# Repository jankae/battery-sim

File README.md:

# battery-sim

## What is it?
The device emulates the behaviour of a battery, essentially it is a two quadrant supply with a configurable internal resistance.

Key features:
* Voltage range: 0 to 18V
* Current range: -3 to +3A
* Resistance range: 0.005 to 6Ohm

## Why was it built?
While developing other hardware meant to test batteries, various batteries in various different states (voltages, internal resistances, ...) were required to test some aspects. Normal batteries could have been used but getting them to (repeatedly!) behave in the necessary way would have been extremely time-consuming. So, this device was created.

It also doubles as a battery charger/discharger and general use supply.

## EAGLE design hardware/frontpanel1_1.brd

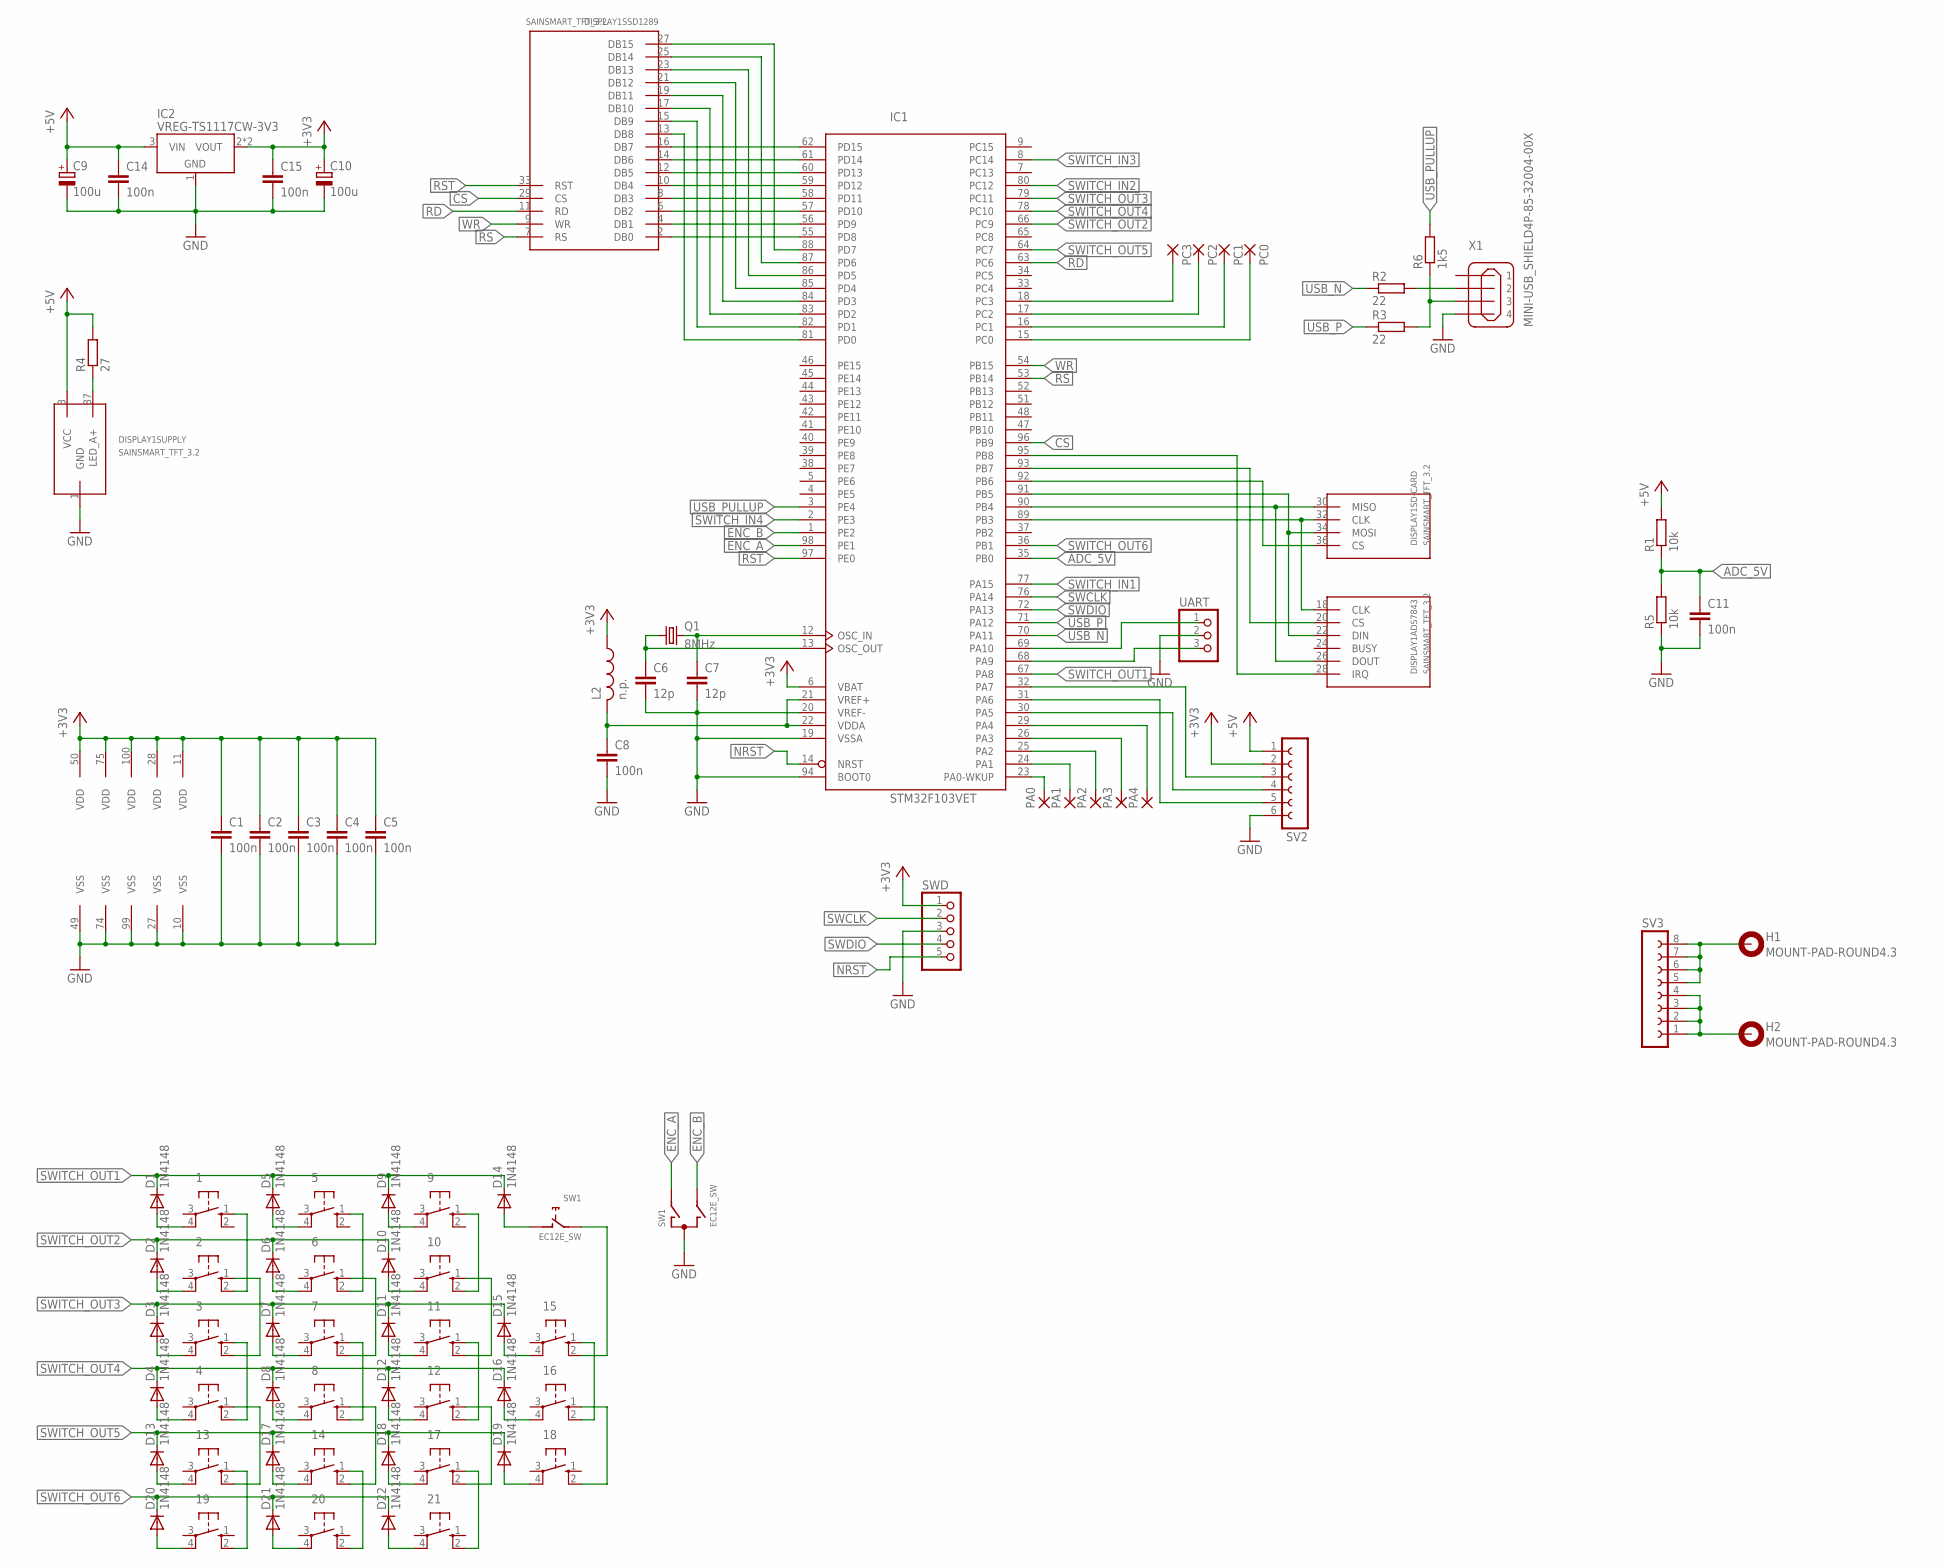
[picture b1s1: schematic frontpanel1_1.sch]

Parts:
1, 2, 3, 4, 5, 6, 7, 8, 9, 10, 11, 12, 13, 14, 15, 16, 17, 18, 19, 20, 21: 10-XXSMD; SMD
C1, C2, C3, C4, C5, C8, C11, C14, C15: 100n; C0603K
C6, C7: 12p; C0603K
C9, C10: 100u; 153CLV-0505
D1, D2, D3, D4, D5, D6, D7, D8, D9, D10, D11, D12, D13, D14, D15, D16, D17, D18, D19, D20, D21, D22: 1N4148; SOD323-W
DISPLAY1: SAINSMART_TFT_3.2
H1, H2: MOUNT-PAD-ROUND4.3; 4,3-PAD
IC1: STM32F103VET; LQFP100
IC2: VREG-TS1117CW-3V3; SOT223
L2: n.p.; R0603
PA0, PA1, PA2, PA3, PA4: SMD2; SMD1,27-2,54
PC0, PC1, PC2, PC3: SMD2; SMD1,27-2,54
Q1: 8MHz; SM49
R1, R5: 10k; R0603
R2, R3: 22; R0603
R4: 27; R1206
R6: 1k5; R0603
SV2: FE06-1; FE06
SV3: FE08-1; FE08
SW1: EC12E_SW; ALPS_EC12E_SW
SWD: PINHD-1X5; 1X05
UART: PINHD-1X3; 1X03
X1: MINI-USB_SHIELD4P-85-32004-00X; 85-32004-00X

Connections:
+3V3: C1.1, C2.1, C3.1, C4.1, C5.1, C10.+, C15.1, IC1.6 (VBAT), IC1.11 (VDD), IC1.28 (VDD), IC1.50 (VDD), IC1.75 (VDD), IC1.100 (VDD), IC2.2 (VOUT), IC2.4 (VOUT), L2.1, SV2.2, SWD.1
+5V: C9.+, C14.1, DISPLAY1.3 (VCC), IC2.3 (VIN), R1.2, R4.2, SV2.1
ADC_5V: C11.1, IC1.35 (PB0), R1.1, R5.2
CS: DISPLAY1.29 (CS), IC1.96 (PB9)
ENC_A: IC1.98 (PE1), SW1.A
ENC_B: IC1.1 (PE2), SW1.B
EXT4: C8.1, IC1.21 (VREF+), IC1.22 (VDDA), L2.2
GND: C1.2, C2.2, C3.2, C4.2, C5.2, C6.2, C7.2, C8.2, C9.-, C10.-, C11.2, C14.2, C15.2, DISPLAY1.1 (GND), IC1.10 (VSS), IC1.19 (VSSA), IC1.20 (VREF-), IC1.27 (VSS), IC1.49 (VSS), IC1.74 (VSS), IC1.94 (BOOT0), IC1.99 (VSS), IC2.1 (GND), R5.1, SV2.6, SW1.C, SWD.3, UART.2, X1.4
MISO: IC1.31 (PA6), SV2.5
MOSI: IC1.32 (PA7), SV2.3
unnamed: IC1.15 (PC0), PC0.1
unnamed: C7.1, IC1.12 (OSC_IN), Q1.2
unnamed: C6.1, IC1.13 (OSC_OUT), Q1.1
unnamed: DISPLAY1.2 (DB0), IC1.55 (PD8)
unnamed: DISPLAY1.4 (DB1), IC1.56 (PD9)
unnamed: DISPLAY1.6 (DB2), IC1.57 (PD10)
unnamed: DISPLAY1.8 (DB3), IC1.58 (PD11)
unnamed: DISPLAY1.10 (DB4), IC1.59 (PD12)
unnamed: DISPLAY1.12 (DB5), IC1.60 (PD13)
unnamed: DISPLAY1.14 (DB6), IC1.61 (PD14)
unnamed: DISPLAY1.16 (DB7), IC1.62 (PD15)
unnamed: DISPLAY1.15 (DB9), IC1.82 (PD1)
unnamed: DISPLAY1.17 (DB10), IC1.83 (PD2)
unnamed: DISPLAY1.13 (DB8), IC1.81 (PD0)
unnamed: DISPLAY1.19 (DB11), IC1.84 (PD3)
unnamed: DISPLAY1.21 (DB12), IC1.85 (PD4)
unnamed: DISPLAY1.23 (DB13), IC1.86 (PD5)
unnamed: DISPLAY1.25 (DB14), IC1.87 (PD6)
unnamed: DISPLAY1.27 (DB15), IC1.88 (PD7)
unnamed: 13.1 (S), 19.2 (S1)
unnamed: 4.1 (S), 13.2 (S1)
unnamed: 13.4 (P1), D13.A
unnamed: 14.4 (P1), D17.A
unnamed: 17.4 (P1), D18.A
unnamed: 18.4 (P1), D19.A
unnamed: 19.4 (P1), D20.A
unnamed: 20.4 (P1), D21.A
unnamed: 21.4 (P1), D22.A
unnamed: IC1.16 (PC1), PC1.1
unnamed: IC1.17 (PC2), PC2.1
unnamed: IC1.18 (PC3), PC3.1
unnamed: IC1.23 (PA0-WKUP), PA0.1
unnamed: 2.1 (S), 3.2 (S1)
unnamed: 1.1 (S), 2.2 (S1)
unnamed: 5.1 (S), 6.2 (S1)
unnamed: 6.1 (S), 7.2 (S1)
unnamed: IC1.24 (PA1), PA1.1
unnamed: 8.1 (S), 14.2 (S1)
unnamed: 14.1 (S), 20.2 (S1)
unnamed: 17.1 (S), 21.2 (S1)
unnamed: IC1.25 (PA2), PA2.1
unnamed: R2.2, X1.2
unnamed: R3.2, R6.1, X1.3
unnamed: DISPLAY1.37 (LED_A+), R4.1
unnamed: IC1.26 (PA3), PA3.1
unnamed: DISPLAY1.22 (DIN), DISPLAY1.34 (MOSI), IC1.91 (PB5)
unnamed: 4.4 (P1), D4.A
unnamed: 3.4 (P1), D3.A
unnamed: 2.4 (P1), D2.A
unnamed: 1.4 (P1), D1.A
unnamed: DISPLAY1.26 (DOUT), DISPLAY1.30 (MISO), IC1.90 (PB4)
unnamed: DISPLAY1.18 (CLK), DISPLAY1.32 (CLK), IC1.89 (PB3)
unnamed: 11.1 (S), 12.2 (S1)
unnamed: 8.4 (P1), D8.A
unnamed: 7.4 (P1), D7.A
unnamed: 6.4 (P1), D6.A
unnamed: 5.4 (P1), D5.A
unnamed: 10.1 (S), 11.2 (S1)
unnamed: 9.1 (S), 10.2 (S1)
unnamed: 15.1 (S), 16.2 (S1)
unnamed: 12.4 (P1), D12.A
unnamed: 11.4 (P1), D11.A
unnamed: 10.4 (P1), D10.A
unnamed: 9.4 (P1), D9.A
unnamed: IC1.29 (PA4), PA4.1
unnamed: DISPLAY1.36 (CS), IC1.92 (PB6)
unnamed: DISPLAY1.20 (CS), IC1.93 (PB7)
unnamed: 16.4 (P1), D16.A
unnamed: 15.4 (P1), D15.A
unnamed: D14.A, SW1.D (1)
unnamed: DISPLAY1.28 (IRQ), IC1.95 (PB8)
unnamed: 15.2 (S1), SW1.E (2)
NRST: IC1.14 (NRST), SWD.5
OUT+: H2.B4,3, SV3.1, SV3.2, SV3.3, SV3.4
OUT-: H1.B4,3, SV3.5, SV3.6, SV3.7, SV3.8
RD: DISPLAY1.11 (RD), IC1.63 (PC6)
RS: DISPLAY1.7 (RS), IC1.53 (PB14)
RST: DISPLAY1.33 (RST), IC1.97 (PE0)
RX: IC1.69 (PA10), UART.1
SCK: IC1.30 (PA5), SV2.4
SWCLK: IC1.76 (PA14), SWD.2
SWDIO: IC1.72 (PA13), SWD.4
SWITCH_IN1: 3.1 (S), 4.2 (S1), IC1.77 (PA15)
SWITCH_IN2: 7.1 (S), 8.2 (S1), IC1.80 (PC12)
SWITCH_IN3: 12.1 (S), 17.2 (S1), IC1.8 (PC14)
SWITCH_IN4: 16.1 (S), 18.2 (S1), IC1.2 (PE3)
SWITCH_OUT1: D1.C, D5.C, D9.C, D14.C, IC1.67 (PA8)
SWITCH_OUT2: D2.C, D6.C, D10.C, IC1.66 (PC9)
SWITCH_OUT3: D3.C, D7.C, D11.C, D15.C, IC1.79 (PC11)
SWITCH_OUT4: D4.C, D8.C, D12.C, D16.C, IC1.78 (PC10)
SWITCH_OUT5: D13.C, D17.C, D18.C, D19.C, IC1.64 (PC7)
SWITCH_OUT6: D20.C, D21.C, D22.C, IC1.36 (PB1)
TX: IC1.68 (PA9), UART.3
USB_N: IC1.70 (PA11), R2.1
USB_P: IC1.71 (PA12), R3.1
USB_PULLUP: IC1.3 (PE4), R6.2
WR: DISPLAY1.9 (WR), IC1.54 (PB15)

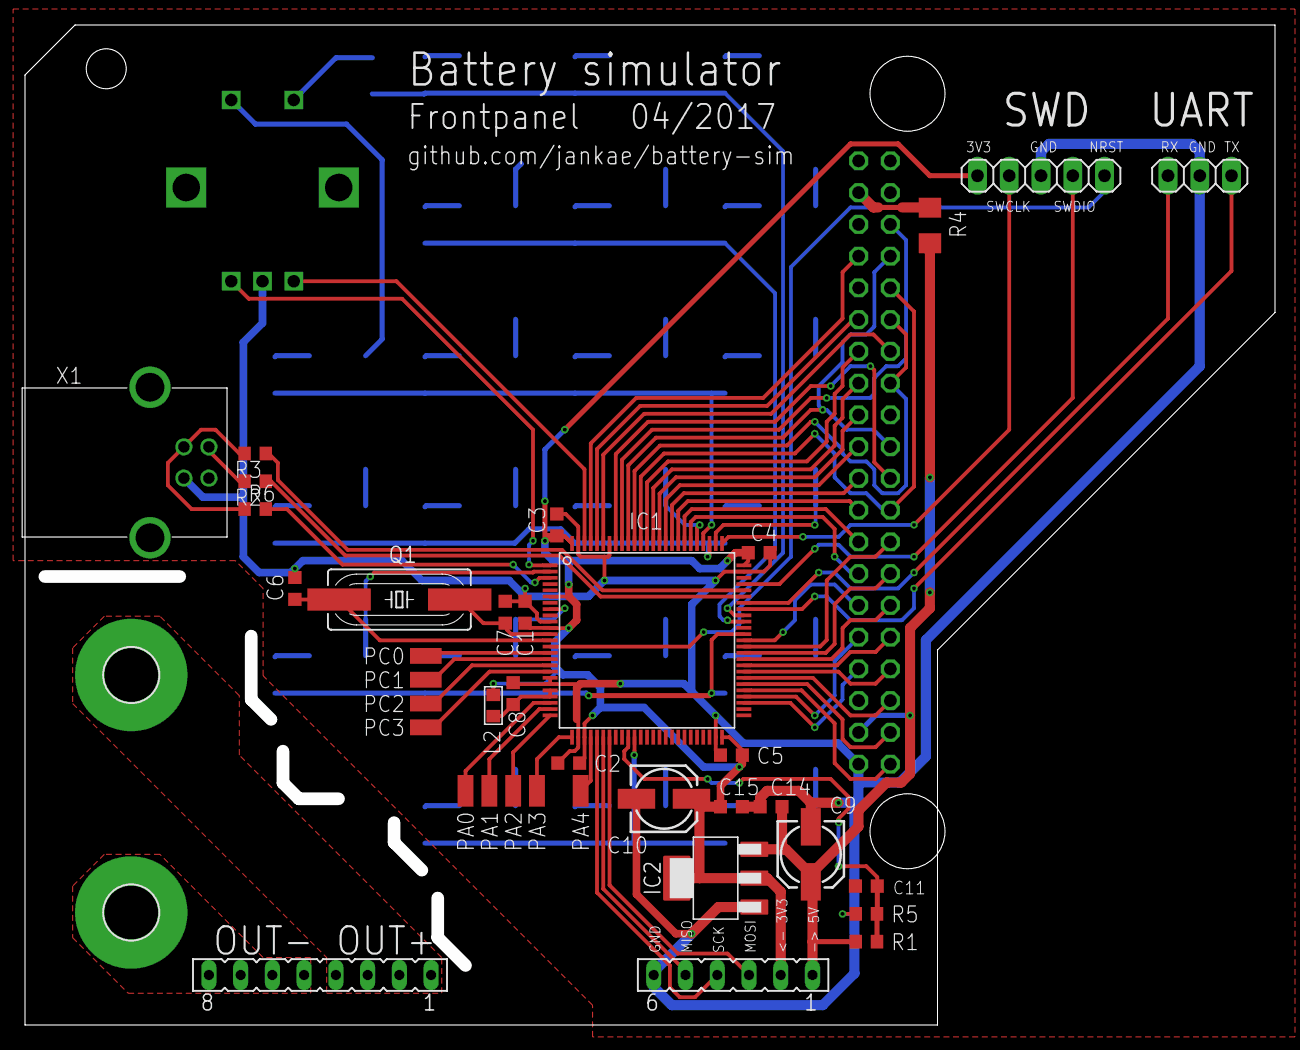
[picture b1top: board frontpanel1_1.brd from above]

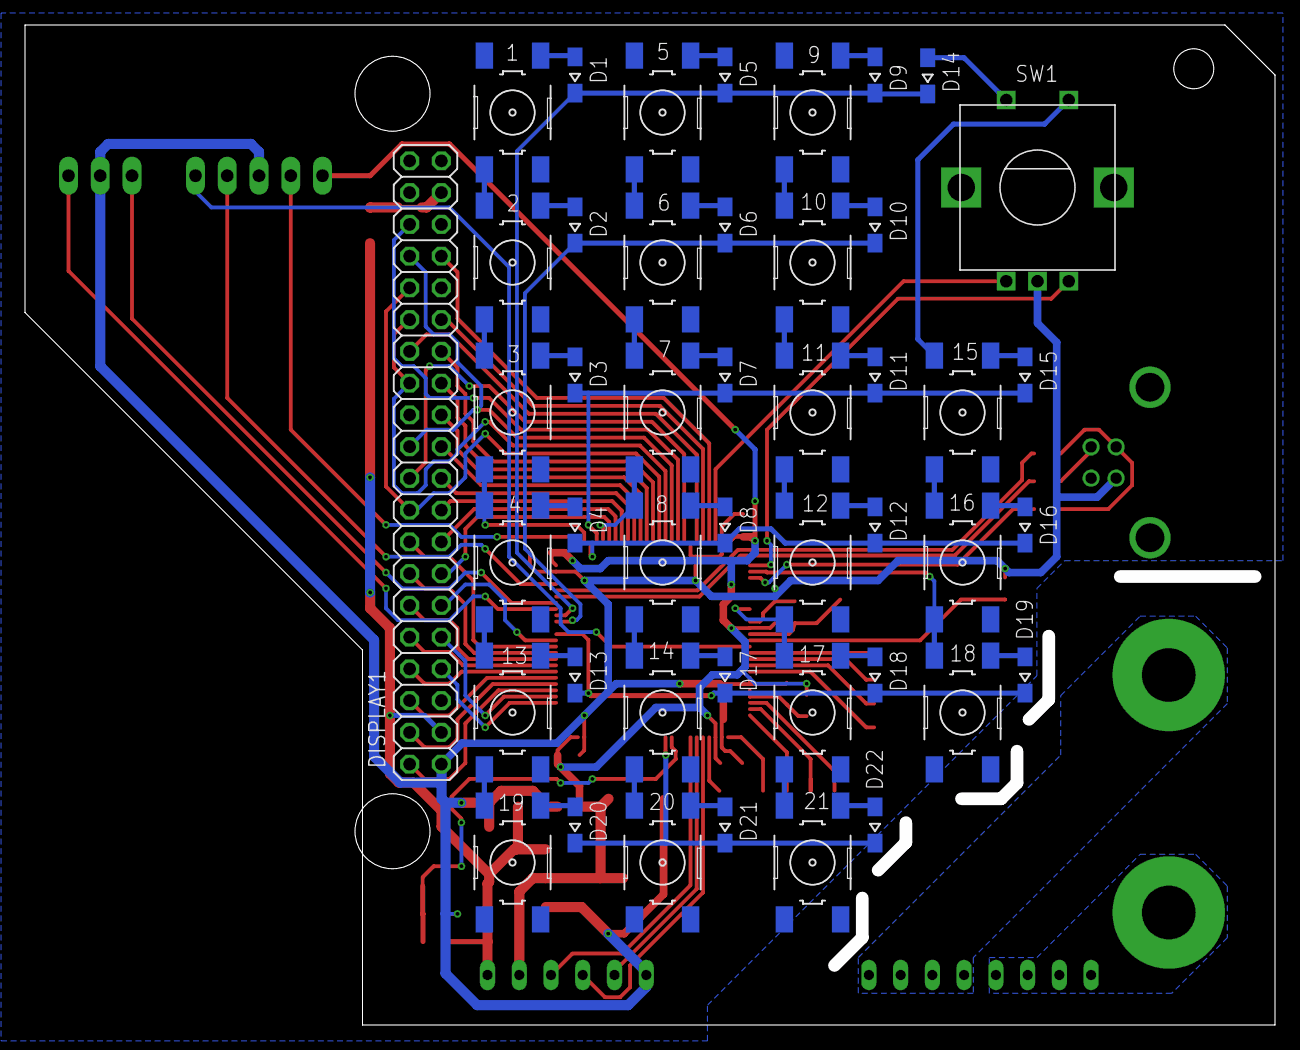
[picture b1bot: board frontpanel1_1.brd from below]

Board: 2 copper layers, 100.0 x 80.0 mm, 84 parts (45 on the bottom side), 107 nets.

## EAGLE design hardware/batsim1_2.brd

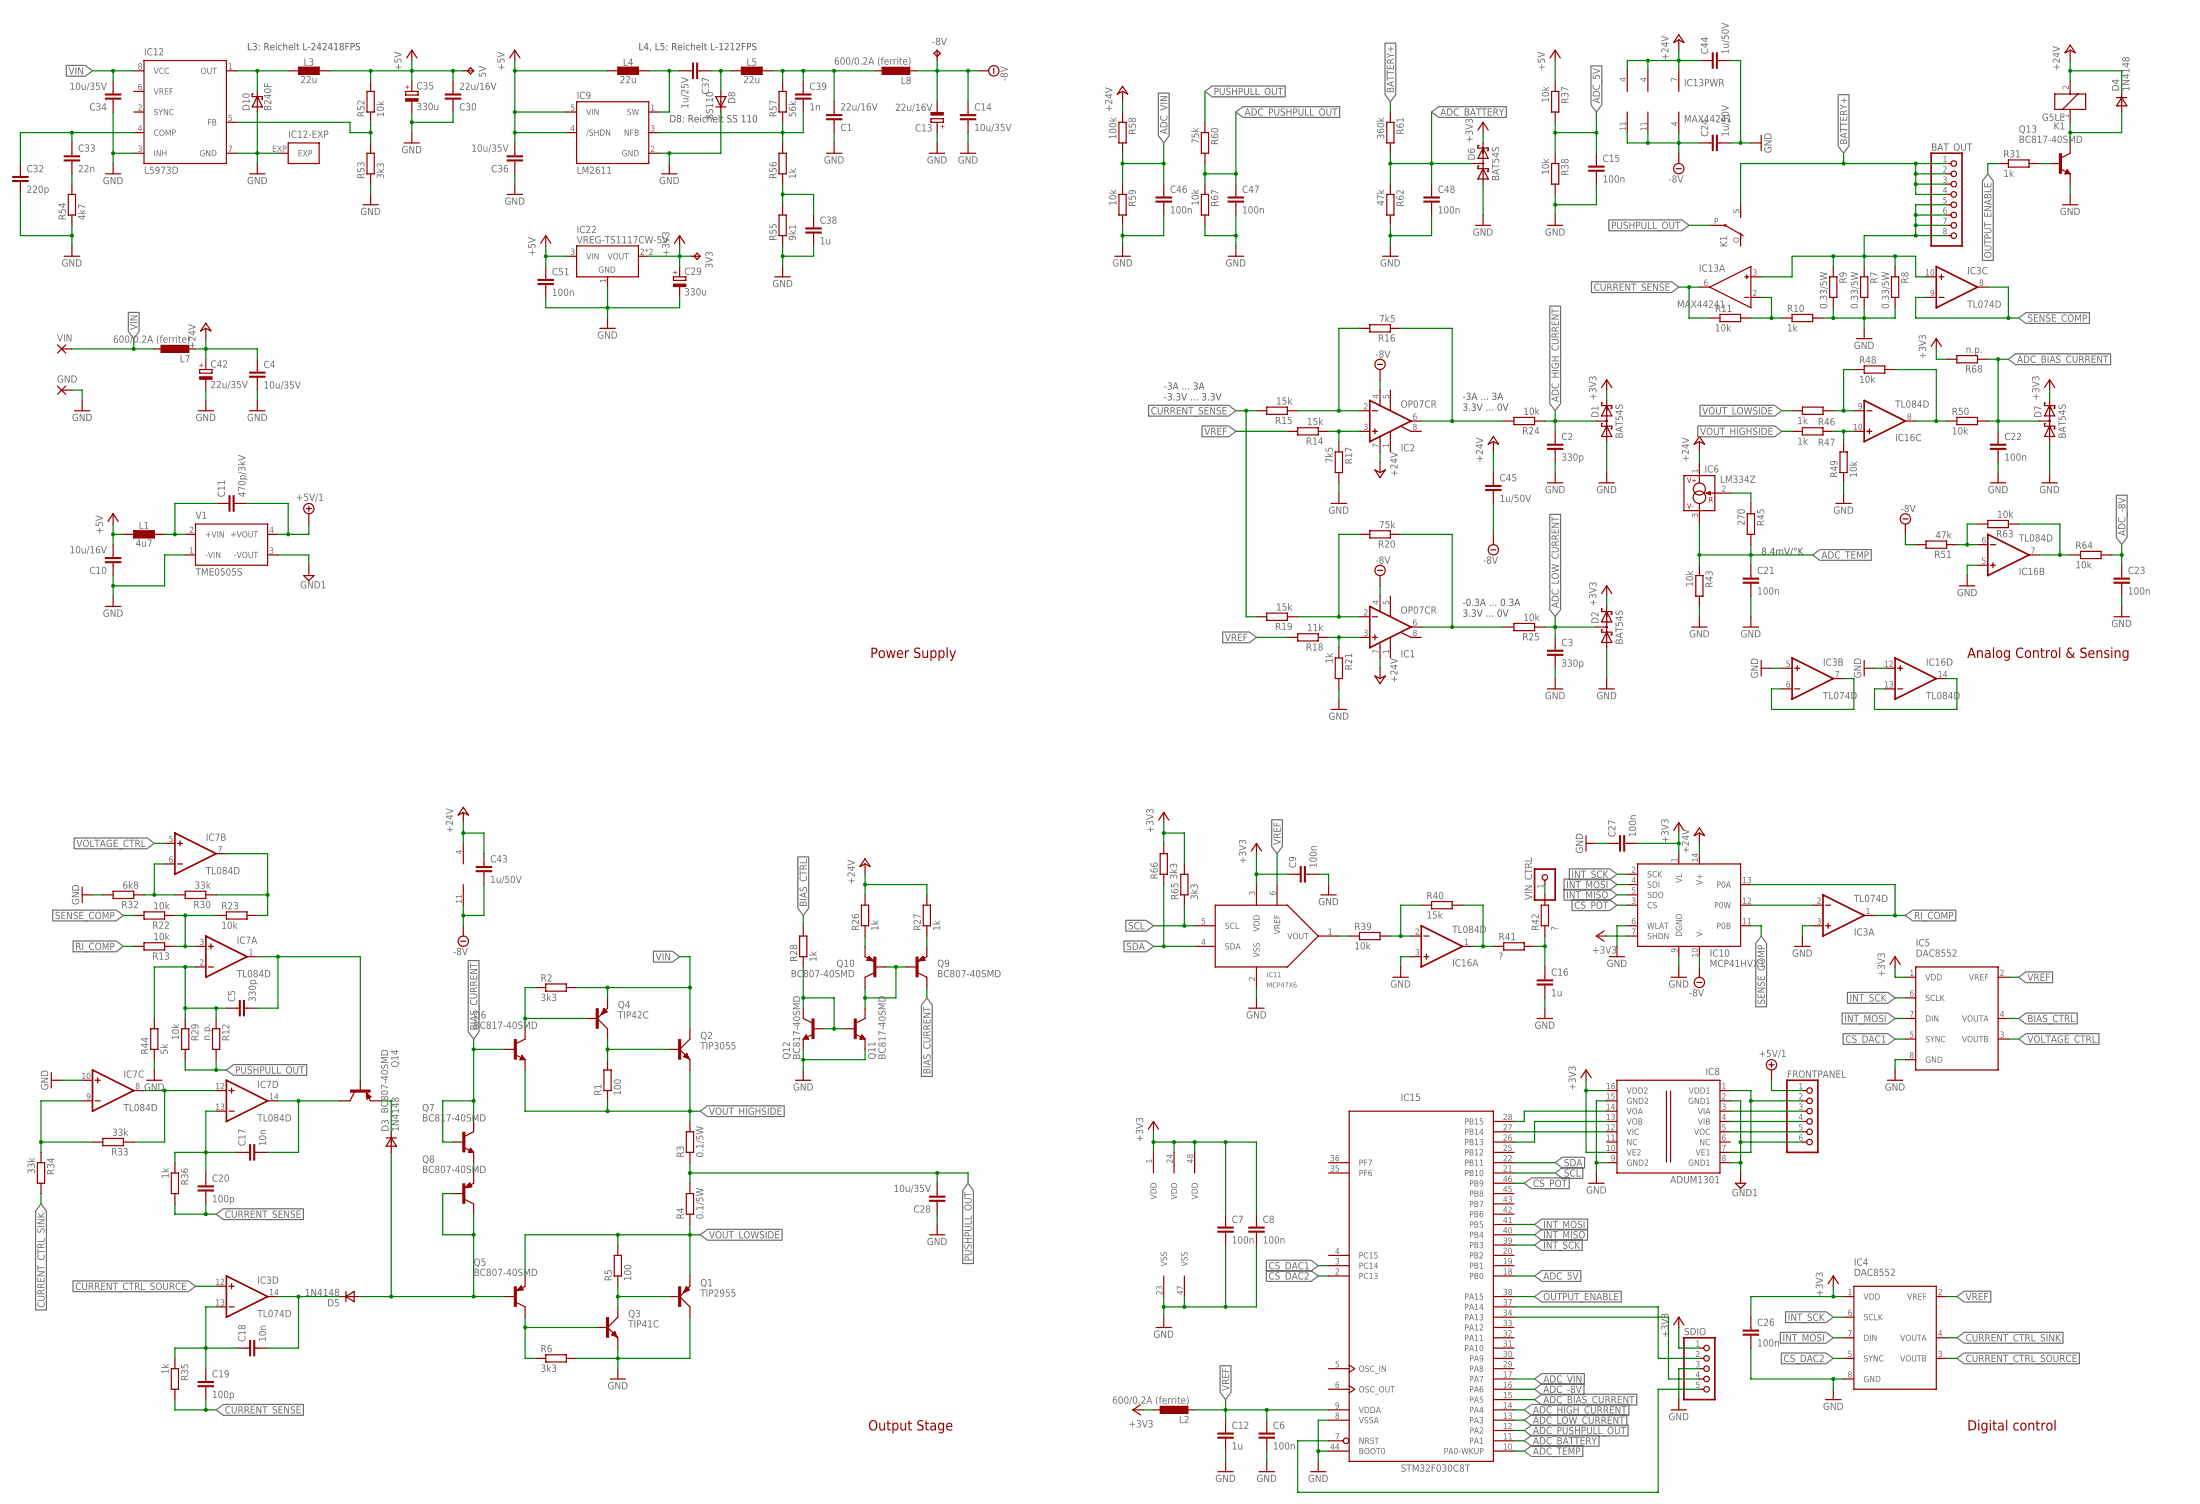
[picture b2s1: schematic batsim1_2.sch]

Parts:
3V3, 5V: TPB1,27; B1,27
-8V: TPB1,27; B1,27
BAT_OUT: PINHD-1X8/90; 1X08/90
C1, C30: 22u/16V; C1206
C2, C3, C5: 330p; C0603
C4, C14, C28, C34, C36: 10u/35V; C1206
C6, C7, C8, C9, C15, C21, C22, C23, C26, C27, C46, C47, C48, C51: 100n; C0603
C10: 10u/16V; C1206
C11: 470p/3kV; C1812
C12, C16, C38: 1u; C0603
C13: 22u/16V; 153CLV-0505
C17, C18: 10n; C0603
C19, C20: 100p; C0603
C24, C43, C44, C45: 1u/50V; C0603
C29, C35: 330u; 153CLV-0605
C32: 220p; C0603
C33: 22n; C0603
C37: 1u/25V; C1206
C39: 1n; C0603
C42: 22u/35V; 153CLV-0605
D1, D2, D6, D7: BAT54S; SOT23
D3, D4, D5: 1N4148; SOD323
D8: SS110; SMA
D10: B240F; SMB
FRONTPANEL: PINHD-1X6/90; 1X06/90
GND: 3,81/1,4
IC1, IC2: OP07CR; SO08
IC3: TL074D; SO14
IC4, IC5: DAC8552; MSOP8
IC6: LM334Z; TO92
IC7, IC16: TL084D; SO14
IC8: ADUM1301; SO-16W
IC9: LM2611; SOT23-5
IC10: MCP41HVX1; TSSOP14
IC11: MCP47X6; SOT23-6L
IC12: L5973D; HSOP8
IC13: MAX44241; UMAX8
IC15: STM32F030C8T; LQFP48
IC22: VREG-TS1117CW-5V; SOT223
K1: G5LE
L1: 4u7; L_1212
L2, L7, L8: 600/0.2A (ferrite); L2012C
L3: 22u; L_NR60XX
L4, L5: 22u; L_1212
Q1: TIP2955; TOP3AV
Q2: TIP3055; TOP3AV
Q3: TIP41C; TO220AV
Q4: TIP42C; TO220AV
Q5, Q8, Q9, Q10, Q14: BC807-40SMD; SOT23-BEC
Q6, Q7, Q11, Q12, Q13: BC817-40SMD; SOT23-BEC
R1, R5: 100; R0603
R2, R6, R53, R65, R66: 3k3; R0603
R3, R4: 0.1/5W; 5WAXIAL
R7, R8, R9: 0.33/5W; 5WAXIAL
R10, R21, R26, R27, R28, R31, R35, R36, R46, R47, R56: 1k; R0603
R11, R13, R22, R23, R24, R25, R29, R37, R38, R39, R43, R48, R49, R50, R52, R59, R63, R64, R67: 10k; R0603
R12, R68: n.p.; R0603
R14, R15, R19, R40: 15k; R0603
R16, R17: 7k5; R0603
R18: 11k; R0603
R20, R60: 75k; R0603
R30, R33, R34: 33k; R0603
R32: 6k8; R0603
R41, R42: ?; R0603
R44: 5k; R0603
R45: 270; R0603
R51, R62: 47k; R0603
R54: 4k7; R0603
R55: 9k1; R0603
R57: 56k; R0603
R58: 100k; R0603
R61: 360k; R0603
SDIO: PINHD-1X5; 1X05
V1: TME0505S; TME
VIN: 3,81/1,4
VIN_CTRL: PINHD-1X1; 1X01

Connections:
+3V3: 3V3.TP, C7.1, C8.1, C9.1, C26.1, C27.2, C29.+, D1.2 (C2), D2.2 (C2), D6.2 (C2), D7.2 (C2), IC4.1 (VDD), IC5.1 (VDD), IC8.10 (VE2), IC8.16 (VDD2), IC10.1 (VL), IC10.7 (SHDN), IC11.3 (VDD), IC15.1 (VDD), IC15.24 (VDD), IC15.48 (VDD), IC22.2 (VOUT), IC22.4 (VOUT), L2.1, R65.2, R66.2, R68.2, SDIO.1
+5V: 5V.TP, C10.2, C30.2, C35.+, C36.2, C51.1, IC9.4 (/SHDN), IC9.5 (VIN), IC22.3 (VIN), L1.1, L3.2, L4.1, R37.1, R52.2
+5V/1: C11.2, FRONTPANEL.1, V1.4 (+VOUT)
+24V: C4.1, C42.+, C43.1, C44.1, C45.1, D4.1 (C), IC1.7 (V+), IC2.7 (V+), IC3.4 (V+), IC6.1 (V+), IC7.4 (V+), IC10.14 (V+), IC13.7 (V+), IC16.4 (V+), K1.2, L7.2, R26.2, R27.2, R58.1
-8V: -8V.TP, C13.-, C14.1, C24.1, C43.2, C45.2, IC1.4 (V-), IC2.4 (V-), IC3.11 (V-), IC7.11 (V-), IC10.10 (V-), IC13.4 (V-), IC16.11 (V-), L8.2, R51.2
ADC_5V: C15.1, IC15.18 (PB0), R37.2, R38.1
ADC_-8V: C23.1, IC15.16 (PA6), R64.2
ADC_BATTERY: C48.1, D6.3 (C1A2), IC15.11 (PA1), R61.2, R62.1
ADC_BIAS_CURRENT: C22.1, D7.3 (C1A2), IC15.15 (PA5), R50.2, R68.1
ADC_HIGH_CURRENT: C2.1, D1.3 (C1A2), IC15.14 (PA4), R24.1
ADC_LOW_CURRENT: C3.1, D2.3 (C1A2), IC15.13 (PA3), R25.1
ADC_PUSHPULL_OUT: C47.1, IC15.12 (PA2), R60.2, R67.1
ADC_TEMP: C21.1, IC6.3 (V-), IC15.10 (PA0-WKUP), R43.1, R45.2
ADC_VIN: C46.1, IC15.17 (PA7), R58.2, R59.1
BATTERY+: BAT_OUT.1, BAT_OUT.2, BAT_OUT.3, BAT_OUT.4, K1.S, R61.1
BIAS_CTRL: IC5.4 (VOUTA), R28.2
BIAS_CURRENT: Q6.B, Q7.B, Q7.C, Q9.C
CS_DAC1: IC5.5 (SYNC), IC15.3 (PC14)
CS_DAC2: IC4.5 (SYNC), IC15.2 (PC13)
CS_POT: IC10.3 (CS), IC15.46 (PB9)
CURRENT_CTRL_SINK: IC4.4 (VOUTA), R34.2
CURRENT_CTRL_SOURCE: IC3.12 (+IN), IC4.3 (VOUTB)
CURRENT_SENSE: C19.2, C20.2, IC13.6 (OUT), R11.1, R15.2, R19.2, R35.2, R36.2
EXT_MISO: IC8.12 (VIC), IC15.27 (PB14)
EXT_MOSI: IC8.14 (VOA), IC15.28 (PB15)
EXT_SCK: IC8.13 (VOB), IC15.26 (PB13)
GND: C1.1, C2.2, C3.2, C4.2, C6.2, C7.2, C8.2, C9.2, C10.1, C12.2, C13.+, C14.2, C15.2, C16.2, C21.2, C22.2, C23.2, C24.2, C26.2, C27.1, C28.1, C29.-, C30.1, C32.2, C34.1, C35.-, C36.1, C38.2, C42.-, C44.2, C46.2, C47.2, C48.2, C51.2, D1.1 (A1), D2.1 (A1), D6.1 (A1), D7.1 (A1), D8.C, D10.A, GND.1, IC3.3 (+IN), IC3.5 (+IN), IC4.8 (GND), IC5.8 (GND), IC7.10 (+IN), IC8.9 (GND2), IC8.15 (GND2), IC9.2 (GND), IC10.6 (WLAT), IC10.9 (DGND), IC11.2 (VSS), IC12.3 (INH), IC12.7 (GND), IC12.EXP, IC15.8 (VSSA), IC15.23 (VSS), IC15.44 (BOOT0), IC15.47 (VSS), IC16.3 (+IN), IC16.5 (+IN), IC16.12 (+IN), IC22.1 (GND), Q1.C, Q3.E, Q11.E, Q12.E, Q13.E, R6.2, R7.2, R8.2, R9.2, R10.2, R17.2, R21.2, R32.2, R38.2, R43.2, R44.1, R49.1, R53.1, R54.1, R55.1, R59.2, R62.2, R67.2, SDIO.3, V1.1 (-VIN)
GND1: FRONTPANEL.6, IC8.2 (GND1), IC8.8 (GND1), V1.3 (-VOUT)
INT_MISO: IC10.5 (SDO), IC15.40 (PB4)
INT_MOSI: IC4.7 (DIN), IC5.7 (DIN), IC10.4 (SDI), IC15.41 (PB5)
INT_SCK: IC4.6 (SCLK), IC5.6 (SCLK), IC10.2 (SCK), IC15.39 (PB3)
LM2611_SW: C37.2, IC9.1 (SW), L4.2
unnamed: IC7.3 (+IN), R13.1, R22.1, R23.1
unnamed: Q2.B, Q4.C, R1.2
unnamed: Q4.B, Q6.C, R2.1
unnamed: IC7.6 (-IN), R30.2, R32.1
unnamed: BAT_OUT.5, BAT_OUT.6, BAT_OUT.7, BAT_OUT.8, IC3.10 (+IN), IC13.3 (IN+), R7.1, R8.1, R9.1
unnamed: IC16.9 (-IN), R46.2, R48.1
unnamed: Q1.B, Q3.C, R5.1
unnamed: C11.1, L1.2, V1.2 (+VIN)
unnamed: Q3.B, Q5.C, R6.1
unnamed: Q7.E, Q8.E
unnamed: IC7.7 (OUT), R23.2, R30.1
unnamed: D3.1 (C), Q14.E
unnamed: D4.2 (A), K1.1, Q13.C
unnamed: IC13.2 (IN-), R10.1, R11.2
unnamed: IC3.6 (-IN), IC3.7 (OUT)
unnamed: IC2.3 (+IN), R14.1, R17.1
unnamed: IC2.2 (-IN), R15.1, R16.2
unnamed: IC2.6 (OUT), R16.1, R24.2
unnamed: IC1.3 (+IN), R18.1, R21.1
unnamed: IC1.2 (-IN), R19.1, R20.2
unnamed: IC1.6 (OUT), R20.1, R25.2
unnamed: IC3.2 (-IN), IC10.12 (P0W)
unnamed: Q9.B, Q10.B, Q10.C, Q11.C
unnamed: Q11.B, Q12.B, Q12.C, R28.1
unnamed: Q13.B, R31.2
unnamed: IC16.13 (-IN), IC16.14 (OUT)
unnamed: Q10.E, R26.1
unnamed: Q9.E, R27.1
unnamed: C32.1, C33.1, IC12.4 (COMP)
unnamed: C5.2, IC7.1 (OUT), Q14.B
unnamed: IC11.1 (VOUT), R39.1
unnamed: IC7.9 (-IN), R33.2, R34.1
unnamed: IC7.8 (OUT), IC7.12 (+IN), R33.1
unnamed: C18.2, D5.1 (C), IC3.14 (OUT)
unnamed: C18.1, C19.1, IC3.13 (-IN), R35.1
unnamed: C17.2, IC7.14 (OUT), Q14.C
unnamed: IC16.2 (-IN), R39.2, R40.1
unnamed: C17.1, C20.1, IC7.13 (-IN), R36.1
unnamed: IC16.1 (OUT), R40.2, R41.1
unnamed: C16.1, R41.2, R42.1
unnamed: FRONTPANEL.2, IC8.1 (VDD1), IC8.7 (VE1)
unnamed: FRONTPANEL.3, IC8.3 (VIA)
unnamed: FRONTPANEL.4, IC8.4 (VIB)
unnamed: FRONTPANEL.5, IC8.5 (VOC)
unnamed: C33.2, R54.2
unnamed: IC16.10 (+IN), R47.2, R49.2
unnamed: IC6.2 (R), R45.1
unnamed: D10.C, IC12.1 (OUT), L3.1
unnamed: C1.2, C39.1, L5.2, L8.1, R57.2
unnamed: IC12.5 (FB), R52.1, R53.2
unnamed: IC16.8 (OUT), R48.2, R50.1
unnamed: C37.1, D8.A, L5.1
unnamed: C39.2, IC9.3 (NFB), R56.2, R57.1
unnamed: C38.1, R55.2, R56.1
unnamed: IC16.6 (-IN), R51.1, R63.2
unnamed: IC16.7 (OUT), R63.1, R64.1
NRST: IC15.7 (NRST), SDIO.5
OUTPUT_ENABLE: IC15.38 (PA15), R31.1
PUSHPULL_CTRL: D3.2 (A), D5.2 (A), Q5.B, Q8.B, Q8.C
PUSHPULL_OUT: C28.2, K1.P, R3.1, R4.2, R12.2, R29.2, R60.1
RI_COMP: IC3.1 (OUT), IC10.13 (P0A), R13.2
SCL: IC11.5 (SCL), IC15.21 (PB10), R65.1
SDA: IC11.4 (SDA), IC15.22 (PB11), R66.1
SENSE_COMP: IC3.8 (OUT), IC3.9 (-IN), IC10.11 (P0B), R22.2
SWCLK: IC15.37 (PA14), SDIO.2
SWDIO: IC15.34 (PA13), SDIO.4
VIN: C34.2, IC12.8 (VCC), L7.1, Q2.C, Q4.E, R2.2, VIN.1
VIN_CTRL: R42.2, VIN_CTRL.1
VOLTAGE_CTRL: IC5.3 (VOUTB), IC7.5 (+IN)
VOLTAGE_FEEDBACK: C5.1, IC7.2 (-IN), R12.1, R29.1, R44.2
VOUT_HIGHSIDE: Q2.E, Q6.E, R1.1, R3.2, R47.1
VOUT_LOWSIDE: Q1.E, Q5.E, R4.1, R5.2, R46.1
VREF: C6.1, C12.1, IC4.2 (VREF), IC5.2 (VREF), IC11.6 (VREF), IC15.9 (VDDA), L2.2, R14.2, R18.2

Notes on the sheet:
Output Stage
Digital control
-3A ... 3A -3.3V ... 3.3V
-3A ... 3A 3.3V ... 0V
-0.3A ... 0.3A 3.3V ... 0V
Analog Control & Sensing
8.4mV/°K
Power Supply
L4, L5: Reichelt L-1212FPS
L3: Reichelt L-242418FPS
D8: Reichelt SS 110

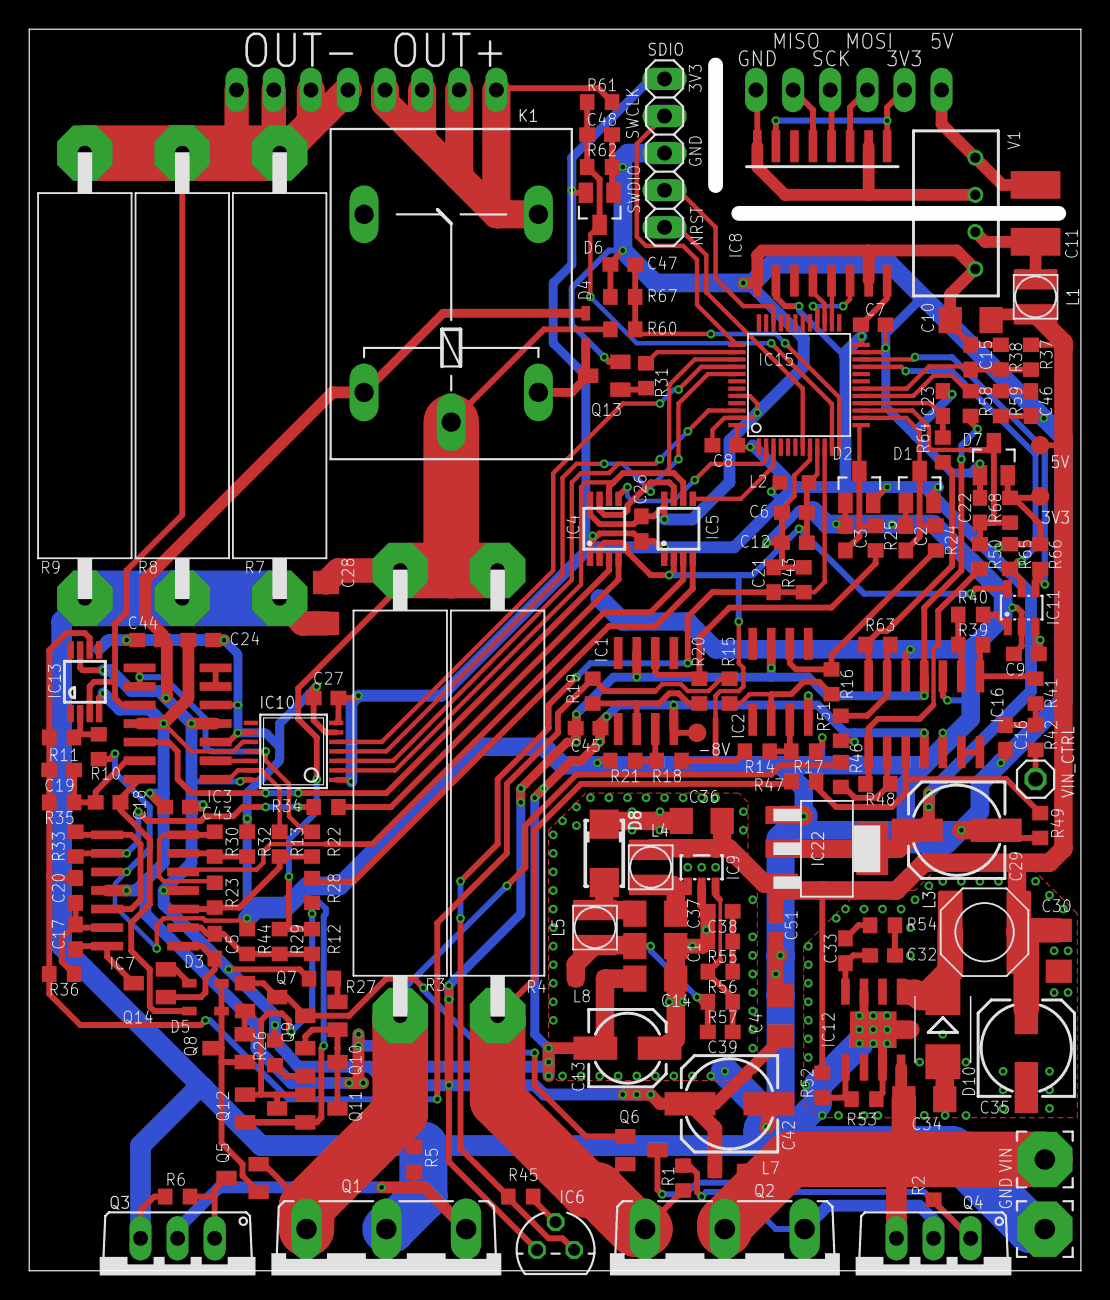
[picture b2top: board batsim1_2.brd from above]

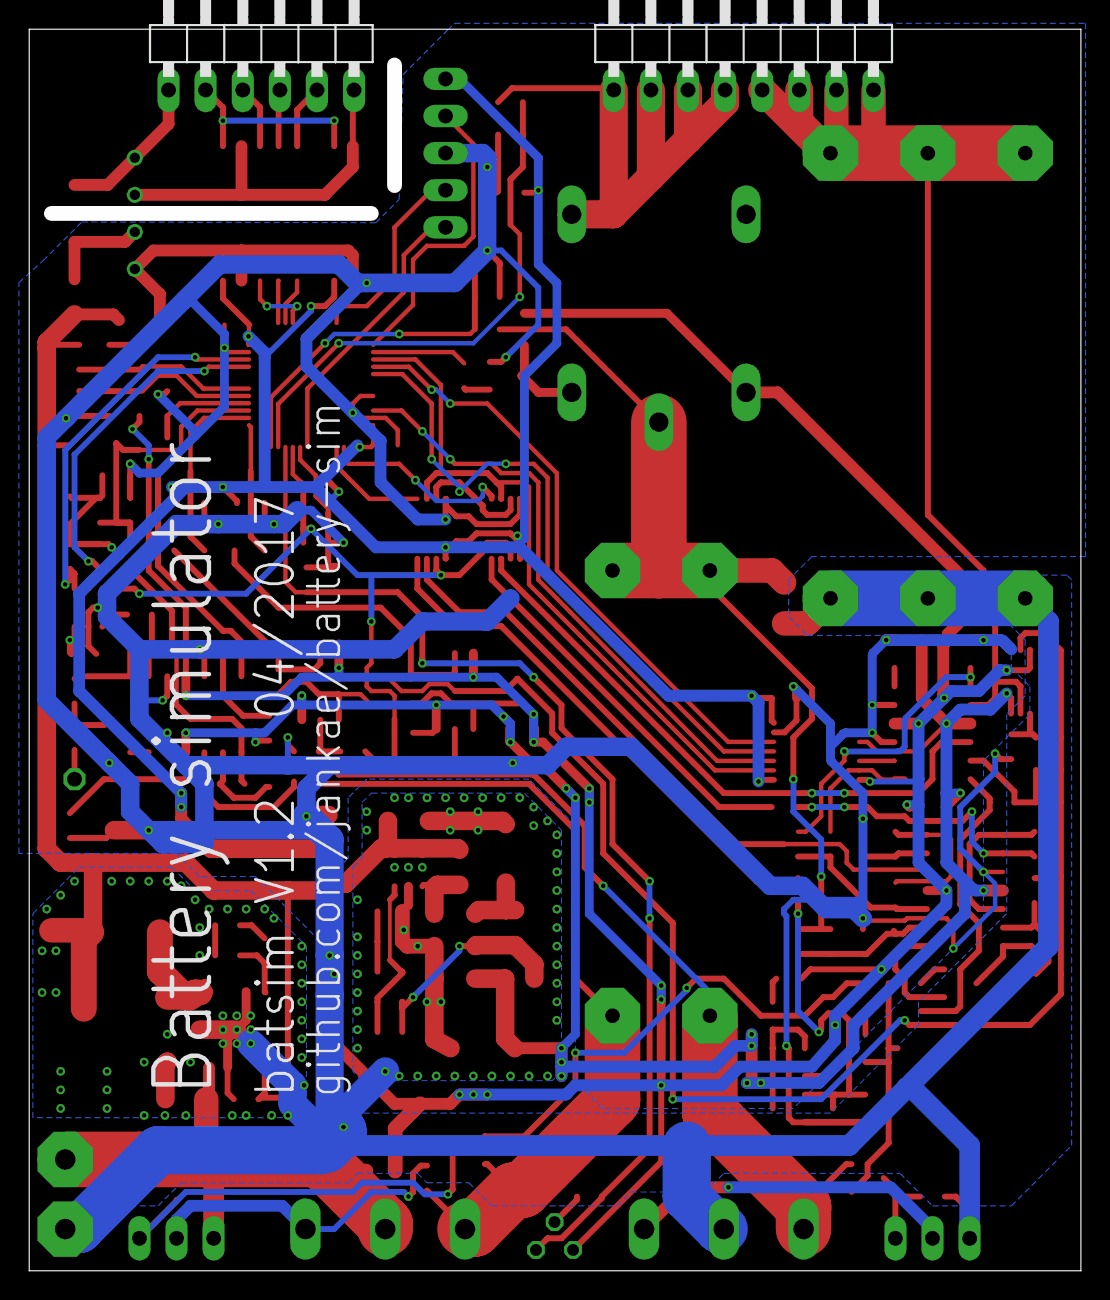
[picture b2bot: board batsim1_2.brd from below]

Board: 2 copper layers, 72.0 x 85.0 mm, 170 parts (2 on the bottom side), 105 nets.

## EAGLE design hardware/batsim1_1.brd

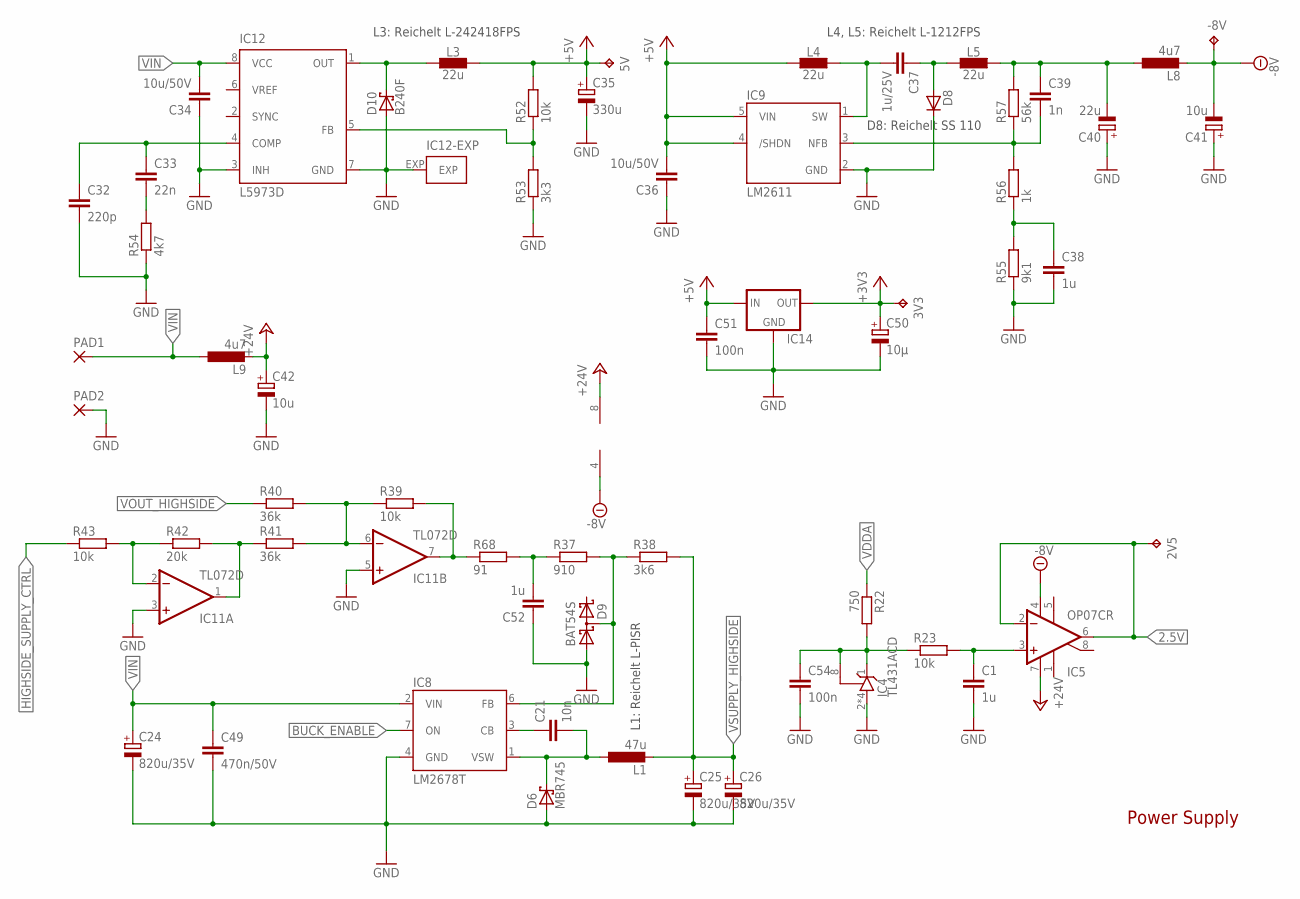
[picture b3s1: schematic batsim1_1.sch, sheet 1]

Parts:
2V5, 3V3, 5V: TPB1,27; B1,27
-8V: TPB1,27; B1,27
C1, C38, C52: 1u; C0603
C21: 10n; C0603
C24, C25, C26: 820u/35V; E5-10,5
C32: 220p; C0603
C33: 22n; C0603
C34, C36: 10u/50V; C1206
C35: 330u; 153CLV-0605
C37: 1u/25V; C1206
C39: 1n; C0603
C40: 22u; 153CLV-0505
C41: 10u; 153CLV-0405
C42: 10u; 153CLV-0505
C49: 470n/50V; C1206
C50: 10µ; SMC_A
C51, C54: 100n; C0603
D6: MBR745; TO220ACS
D8: D-SMA; SMA
D9: BAT54S; SOT23
D10: B240F; SMB
IC4: TL431ACD; SO8
IC5: OP07CR; SO08
IC8: LM2678T; TO220-7
IC9: LM2611; SOT23-5
IC11: TL072D; SO08
IC12: L5973D; HSOP8
IC14: LM1117; SOT223
L1: 47u; PISR
L3: 22u; L_NR60XX
L4, L5: 22u; L_1212
L8, L9: 4u7; L2012C
PAD1, PAD2: 3,81/1,4
R22: 750; R0603
R23, R39, R43, R52: 10k; R0603
R37: 910; R0603
R38: 3k6; R0603
R40, R41: 36k; R0603
R42: 20k; R0603
R53: 3k3; R0603
R54: 4k7; R0603
R55: 9k1; R0603
R56: 1k; R0603
R57: 56k; R0603
R68: 91; R0603

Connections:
2.5V: 2V5.TP, IC5.2 (-IN), IC5.6 (OUT); also elsewhere on the board
+3V3: 3V3.TP, C50.+, IC14.2 (OUT); also elsewhere on the board
+5V: 5V.TP, C35.+, C36.2, C51.1, IC9.4 (/SHDN), IC9.5 (VIN), IC14.3 (IN), L3.2, L4.1, R52.2; also elsewhere on the board
+24V: C42.+, IC5.7 (V+), IC11.8 (V+), L9.2; also elsewhere on the board
-8V: -8V.TP, C41.-, IC5.4 (V-), IC11.4 (V-), L8.2; also elsewhere on the board
BUCK_ENABLE: IC8.7 (ON); also elsewhere on the board
GND: C1.2, C24.-, C25.-, C26.-, C32.2, C34.1, C35.-, C36.1, C38.2, C40.+, C41.+, C42.-, C49.2, C50.-, C51.2, C52.1, C54.2, D6.A, D8.C, D9.1 (A1), D10.A, IC4.2 (A), IC4.3 (A), IC4.6 (A), IC4.7 (A), IC8.4 (GND), IC9.2 (GND), IC11.3 (+IN), IC11.5 (+IN), IC12.3 (INH), IC12.7 (GND), IC12.EXP, IC14.1 (GND), PAD2.1, R53.1, R54.1, R55.1; also elsewhere on the board
HIGHSIDE_SUPPLY_CTRL: R43.1; also elsewhere on the board
LM2611_SW: C37.2, IC9.1 (SW), L4.2
unnamed: C54.1, IC4.1 (C), IC4.8 (R), R22.2, R23.1
unnamed: C1.1, IC5.3 (+IN), R23.2
unnamed: C32.1, C33.1, IC12.4 (COMP)
unnamed: C21.2, D6.C, IC8.1 (VSW), L1.1
unnamed: C21.1, IC8.3 (CB)
unnamed: D9.3 (C1A2), IC8.6 (FB), R37.2, R38.1
unnamed: IC11.7 (OUT), R39.2, R68.1
unnamed: IC11.6 (-IN), R39.1, R40.2, R41.2
unnamed: IC11.1 (OUT), R41.1, R42.2
unnamed: IC11.2 (-IN), R42.1, R43.2
unnamed: C33.2, R54.2
unnamed: D10.C, IC12.1 (OUT), L3.1
unnamed: C39.1, C40.-, L5.2, L8.1, R57.2
unnamed: IC12.5 (FB), R52.1, R53.2
unnamed: C37.1, D8.A, L5.1
unnamed: C39.2, IC9.3 (NFB), R56.2, R57.1
unnamed: C38.1, R55.2, R56.1
unnamed: C52.2, R37.1, R68.2
VDDA: R22.1; also elsewhere on the board
VIN: C24.+, C34.2, C49.1, IC8.2 (VIN), IC12.8 (VCC), L9.1, PAD1.1
VOUT_HIGHSIDE: R40.1; also elsewhere on the board
VSUPPLY_HIGHSIDE: C25.+, C26.+, L1.2, R38.2; also elsewhere on the board

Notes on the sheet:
Power Supply
L4, L5: Reichelt L-1212FPS
L3: Reichelt L-242418FPS
L1: Reichelt L-PISR
D8: Reichelt SS 110

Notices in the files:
parts and their libraries:
xmaker: Licensing: CC v3.0 Attribution-Share Alike
http://creativecommons.org/licenses/by-sa/3.0
